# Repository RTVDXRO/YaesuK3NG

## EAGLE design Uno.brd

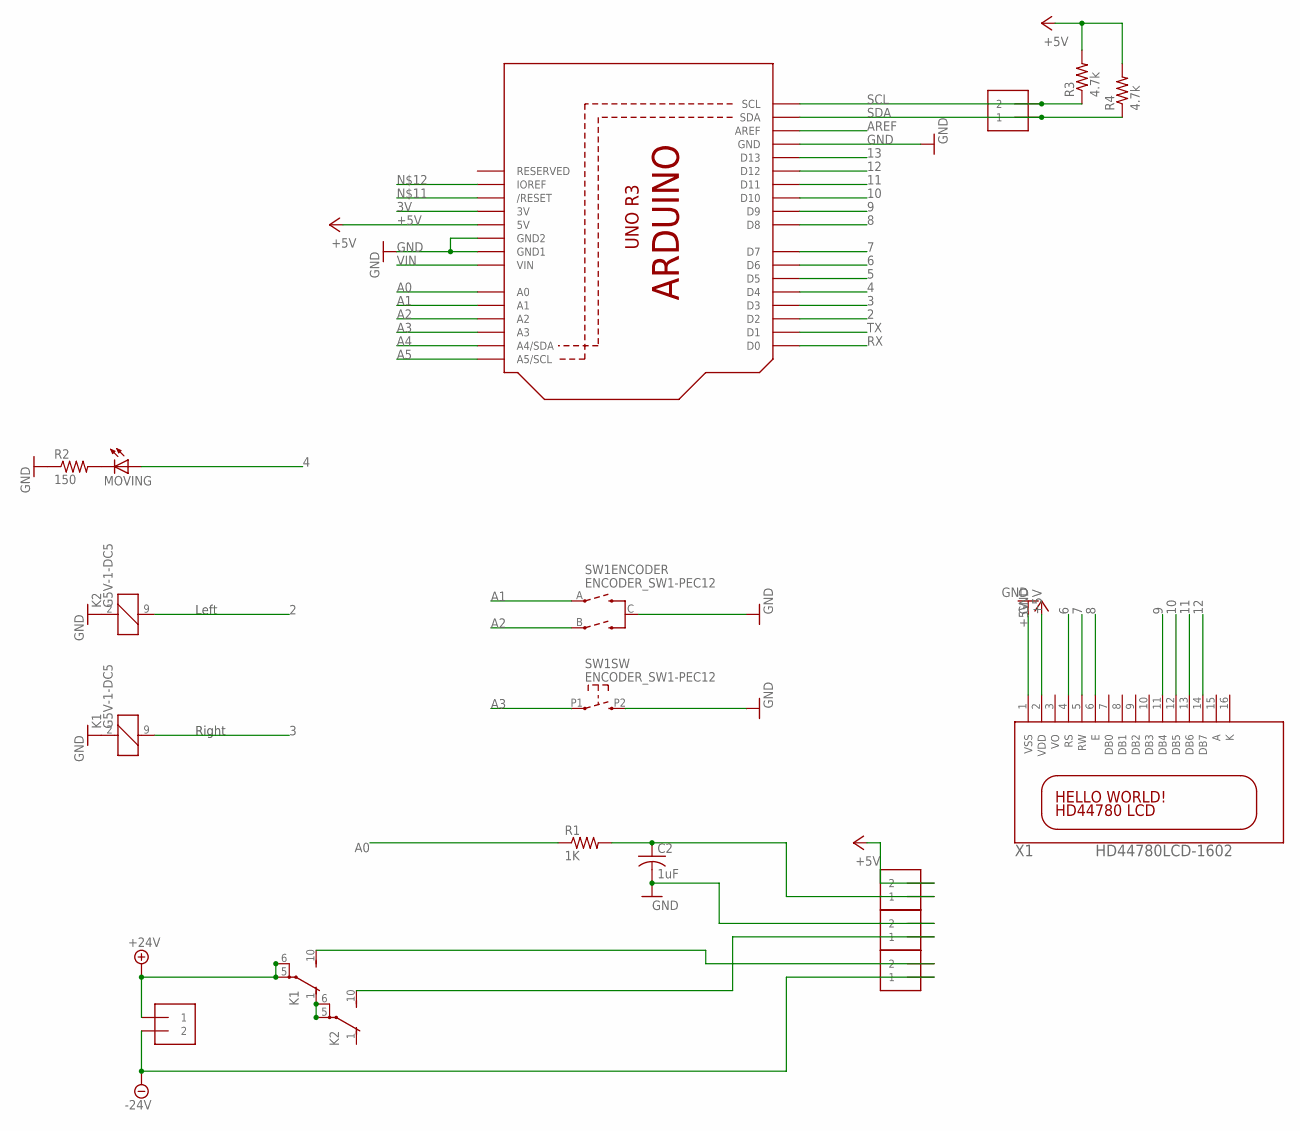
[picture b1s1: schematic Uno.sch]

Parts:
C2: 1uF; C050-024X044
J1, J2, J3, J4, J5: 1X2-3.5MM
K1, K2: G5V-1-DC5; G5V1
MOVING: LED5MM
R1: 1K; 0414V
R2: 150; 0207/5V
R3, R4: 4.7k; 0207/5V
SW1: ENCODER_SW1-PEC12; PEC12_INCREMENTAL_ENCODER
U1: ARDUINOR3-BPLACE
X1: HD44780LCD-1602; LCD1602

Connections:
2: K2.9 (2), U1.D2
3: K1.9 (2), U1.D3
3V: U1.3V
4: MOVING.A, U1.D4
5: U1.D5
6: U1.D6, X1.4 (RS)
7: U1.D7, X1.5 (RW)
8: U1.D8, X1.6 (E)
9: U1.D9, X1.11 (DB4)
10: U1.D10, X1.12 (DB5)
11: U1.D11, X1.13 (DB6)
12: U1.D12, X1.14 (DB7)
13: U1.D13
+5V: J5.2, R3.2, R4.2, U1.5V, X1.2 (VDD)
+24V: J2.1, K1.5, K1.6
-24V: J2.2, J3.1
A0: R1.1, U1.A0
A1: SW1.A, U1.A1
A2: SW1.B, U1.A2
A3: SW1.P1 (1), U1.A3
A4: U1.A4 (A4/SDA)
A5: U1.A5 (A5/SCL)
AREF: U1.AREF
GND: C2.2, J4.2, K1.2 (1), K2.2 (1), R2.1, SW1.C, SW1.P2 (2), U1.GND, U1.GND1, U1.GND2, X1.1 (VSS)
unnamed: MOVING.K (C), R2.2
unnamed: K1.1 (O), K2.5, K2.6
unnamed: J3.2, K1.10 (S)
unnamed: J4.1, K2.10 (S)
unnamed: C2.1, J5.1, R1.2
RX: U1.D0
SCL: J1.2, R3.1, U1.SCL
SDA: J1.1, R4.1, U1.SDA
TX: U1.D1
VIN: U1.VIN

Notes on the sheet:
Right
Left

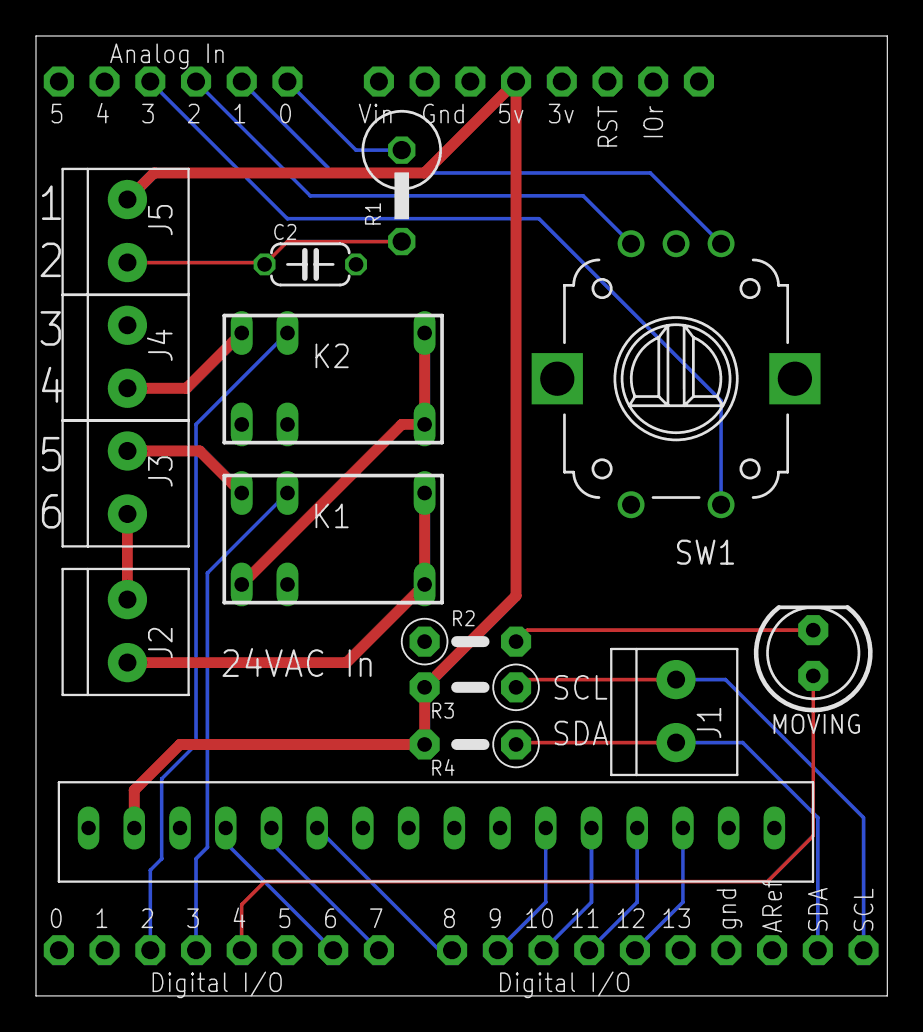
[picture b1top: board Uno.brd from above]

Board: 2 copper layers, 47.3 x 53.3 mm, 16 parts (0 on the bottom side), 25 nets.

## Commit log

2014-03-04 Initial Upload
